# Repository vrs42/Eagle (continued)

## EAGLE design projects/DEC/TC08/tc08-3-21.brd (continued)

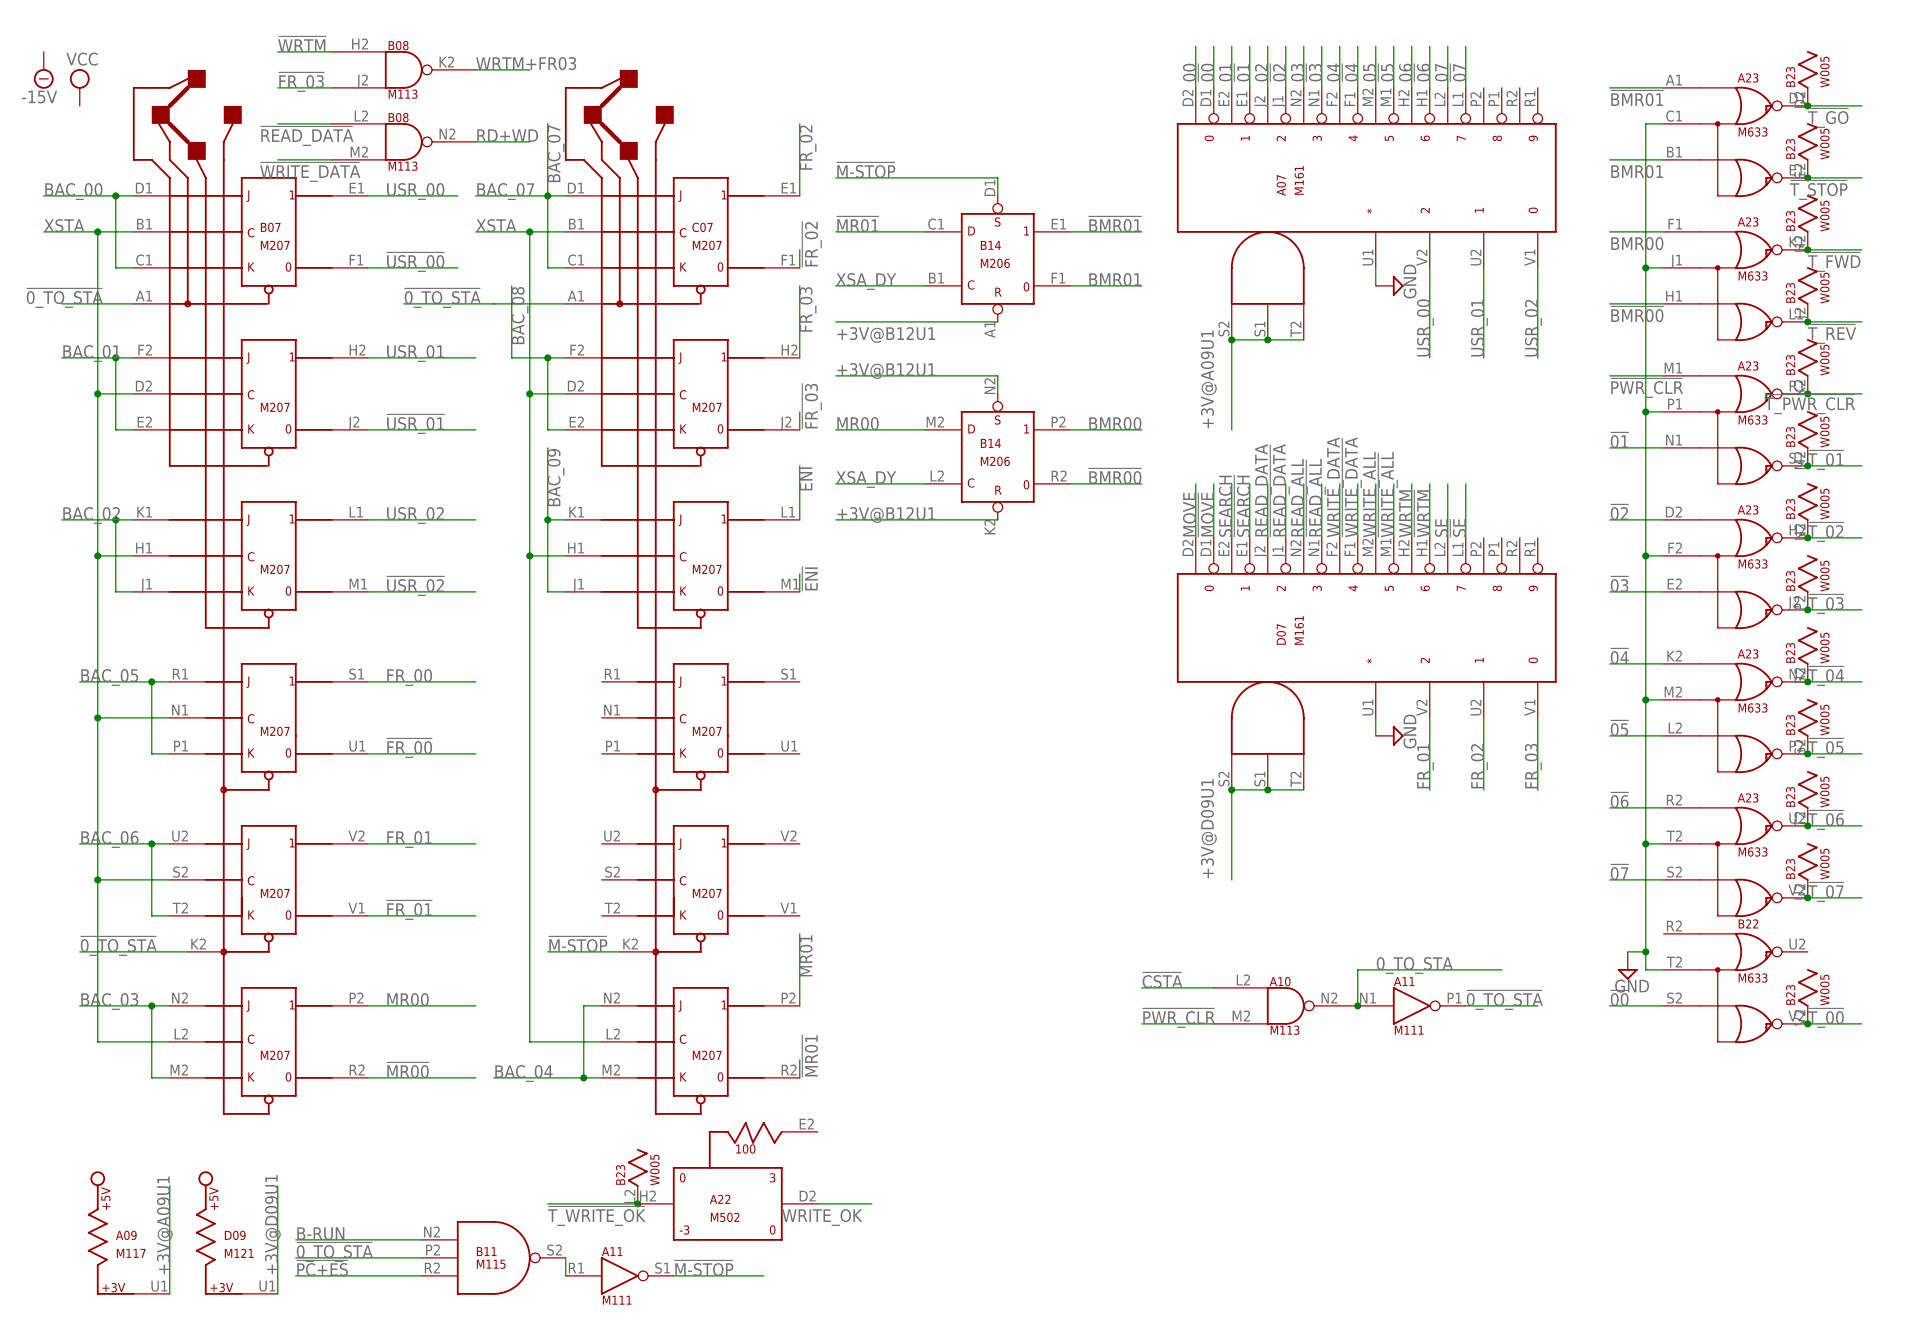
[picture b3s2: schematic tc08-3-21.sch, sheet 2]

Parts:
A07: M161; H807
A09: M117; H807
A10: M113; H807
A11: M111; H807
A22: M502; H807
A23: M633; H807
B07: M207; H807
B08: M113; H807
B11: M115; H807
B14: M206; H807
B22: M633; H807
B23: W005; H807
C07: M207; H807
D07: M161; H807
D09: M121; H807

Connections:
00: A07.D2 (O0)
0_TO_STA: A10.N2 (OUT), A11.N1 (IN)
01: A07.E2 (O1)
02: A07.J2 (O2)
03: A07.N2 (O3)
04: A07.F2 (O4)
05: A07.M2 (O5)
06: A07.H2 (O6)
07: A07.L2 (O7)
!00: A07.D1 (!O0), B22.S2 (B)
!0_TO_STA: A11.P1 (OUT), B07.A1, B07.K2, B11.P2 (IN2), C07.A1
!01: A07.E1 (!O1), A23.N1 (B)
!02: A07.J1 (!O2), A23.D2 (A)
!03: A07.N1 (!O3), A23.E2 (B)
!04: A07.F1 (!O4), A23.K2 (A)
!05: A07.M1 (!O5), A23.L2 (B)
!06: A07.H1 (!O6), A23.R2 (A)
!07: A07.L1 (!O7), A23.S2 (B)
!BMR00: A23.H1 (B), B14.R2 (0)
!BMR01: A23.A1 (A), B14.E1 (1)
!CSTA: A10.L2 (IN1); also elsewhere on the board
!ENI: C07.M1; also elsewhere on the board
!FR_00: B07.U1; also elsewhere on the board
!FR_01: B07.V1; also elsewhere on the board
!FR_02: C07.F1; also elsewhere on the board
!FR_03: B08.J2 (IN2), C07.J2; also elsewhere on the board
!M-STOP: A11.S1 (OUT), B14.D1 (S), C07.K2; also elsewhere on the board
!MOVE: D07.D1 (!O0); also elsewhere on the board
!MR00: B07.R2; also elsewhere on the board
!MR01: B14.C1 (D), C07.R2; also elsewhere on the board
!PC+ES: B11.R2 (IN3); also elsewhere on the board
!PWR_CLR: A10.M2 (IN2), A23.M1 (A); also elsewhere on the board
!READ_ALL: D07.N1 (!O3); also elsewhere on the board
!READ_DATA: B08.L2 (IN1), D07.J1 (!O2); also elsewhere on the board
!SE: D07.L1 (!O7); also elsewhere on the board
!SEARCH: D07.E1 (!O1); also elsewhere on the board
!T_00: B22.V2 (E), B23.V2; also elsewhere on the board
!T_01: A23.S1 (E), B23.M2; also elsewhere on the board
!T_02: A23.H2 (D), B23.N2; also elsewhere on the board
!T_03: A23.J2 (E), B23.P2; also elsewhere on the board
!T_04: A23.N2 (D), B23.R2; also elsewhere on the board
!T_05: A23.P2 (E), B23.S2; also elsewhere on the board
!T_06: A23.U2 (D), B23.T2; also elsewhere on the board
!T_07: A23.V2 (E), B23.U2; also elsewhere on the board
!T_FWD: A23.K1 (D), B23.H2; also elsewhere on the board
!T_GO: A23.D1 (D), B23.D2; also elsewhere on the board
!T_PWR_CLR: A23.R1 (D), B23.K2; also elsewhere on the board
!T_REV: A23.L1 (E), B23.J2; also elsewhere on the board
!T_STOP: A23.E1 (E), B23.E2; also elsewhere on the board
!T_WRITE_OK: A22.H2, B23.L2; also elsewhere on the board
!USR_00: B07.F1; also elsewhere on the board
!USR_01: B07.J2; also elsewhere on the board
!USR_02: B07.M1; also elsewhere on the board
!WRITE_ALL: D07.M1 (!O5)
!WRITE_DATA: B08.M2 (IN2), D07.F1 (!O4)
!WRTM: B08.H2 (IN1), D07.H1 (!O6); also elsewhere on the board
+3V@A09U1: A07.S1 (EN2), A07.S2 (EN1), A07.T2 (EN3), A09.U1; also elsewhere on the board
+3V@B12U1: B14.A1 (R), B14.K2 (R), B14.N2 (S); also elsewhere on the board
+3V@D09U1: D07.S1 (EN2), D07.S2 (EN1), D07.T2 (EN3), D09.U1
-15V: A22.B2 (-15V), A23.B2 (-15V), B22.B2 (-15V), B23.B2 (-15V); also elsewhere on the board
B-RUN: B11.N2 (IN1); also elsewhere on the board
BAC_00: B07.C1, B07.D1; also elsewhere on the board
BAC_01: B07.E2, B07.F2; also elsewhere on the board
BAC_02: B07.J1, B07.K1; also elsewhere on the board
BAC_03: B07.M2, B07.N2; also elsewhere on the board
BAC_04: C07.M2, C07.N2; also elsewhere on the board
BAC_05: B07.P1, B07.R1; also elsewhere on the board
BAC_06: B07.T2, B07.U2; also elsewhere on the board
BAC_07: C07.C1, C07.D1; also elsewhere on the board
BAC_08: C07.E2, C07.F2; also elsewhere on the board
BAC_09: C07.J1, C07.K1; also elsewhere on the board
BMR00: A23.F1 (A), B14.P2 (1)
BMR01: A23.B1 (B), B14.F1 (0)
ENI: C07.L1; also elsewhere on the board
FR_00: B07.S1; also elsewhere on the board
FR_01: B07.V2, D07.V2 (IN2); also elsewhere on the board
FR_02: C07.E1, D07.U2 (IN1); also elsewhere on the board
FR_03: C07.H2, D07.V1 (IN0); also elsewhere on the board
GND: A07.C2 (GND), A07.T1 (GND), A07.U1 (IN*), A09.C2 (GND), A09.T1 (GND), A10.C2 (GND), A10.T1 (GND), A11.C2 (GND), A11.T1 (GND), A22.C2 (GND), A22.M2 (GND), A23.C1 (C), A23.C2 (GND), A23.F2 (C), A23.J1 (C), A23.M2 (C), A23.P1 (C), A23.T1 (GND), A23.T2 (C), A23.U1 (GND), A23.V1 (GND), B07.C2 (GND), B07.T1 (GND), B08.C2 (GND), B08.T1 (GND), B11.C2 (GND), B11.T1 (GND), B14.C2 (GND), B14.T1 (GND), B22.C2 (GND), B22.T1 (GND), B22.T2 (C), B22.U1 (GND), B22.V1 (GND), B23.C2 (GND), C07.C2 (GND), C07.T1 (GND), D07.C2 (GND), D07.T1 (GND), D07.U1 (IN*), D09.C2 (GND), D09.T1 (GND); also elsewhere on the board
MOVE: D07.D2 (O0)
MR00: B07.P2, B14.M2 (D); also elsewhere on the board
MR01: C07.P2; also elsewhere on the board
unnamed: A11.R1 (IN), B11.S2 (OUT)
RD+WD: B08.N2 (OUT); also elsewhere on the board
READ_ALL: D07.N2 (O3)
READ_DATA: D07.J2 (O2); also elsewhere on the board
SE: D07.L2 (O7)
SEARCH: D07.E2 (O1); also elsewhere on the board
USR_00: A07.V2 (IN2), B07.E1; also elsewhere on the board
USR_01: A07.U2 (IN1), B07.H2; also elsewhere on the board
USR_02: A07.V1 (IN0), B07.L1; also elsewhere on the board
VCC: A07.A2 (VCC), A09.A2 (VCC), A10.A2 (VCC), A11.A2 (VCC), A22.A2 (VCC), A23.A2 (VCC), B07.A2 (VCC), B08.A2 (VCC), B11.A2 (VCC), B14.A2 (VCC), B22.A2 (VCC), B23.A2 (VCC), C07.A2 (VCC), D07.A2 (VCC), D09.A2 (VCC); also elsewhere on the board
WRITE_ALL: D07.M2 (O5); also elsewhere on the board
WRITE_DATA: D07.F2 (O4); also elsewhere on the board
WRITE_OK: A22.D2; also elsewhere on the board
WRTM: D07.H2 (O6); also elsewhere on the board
WRTM+FR03: B08.K2 (OUT); also elsewhere on the board
XSA_DY: B14.B1 (C), B14.L2 (C); also elsewhere on the board
XSTA: B07.B1, B07.D2, B07.H1, B07.L2, B07.N1, B07.S2, C07.B1, C07.D2, C07.H1, C07.L2; also elsewhere on the board

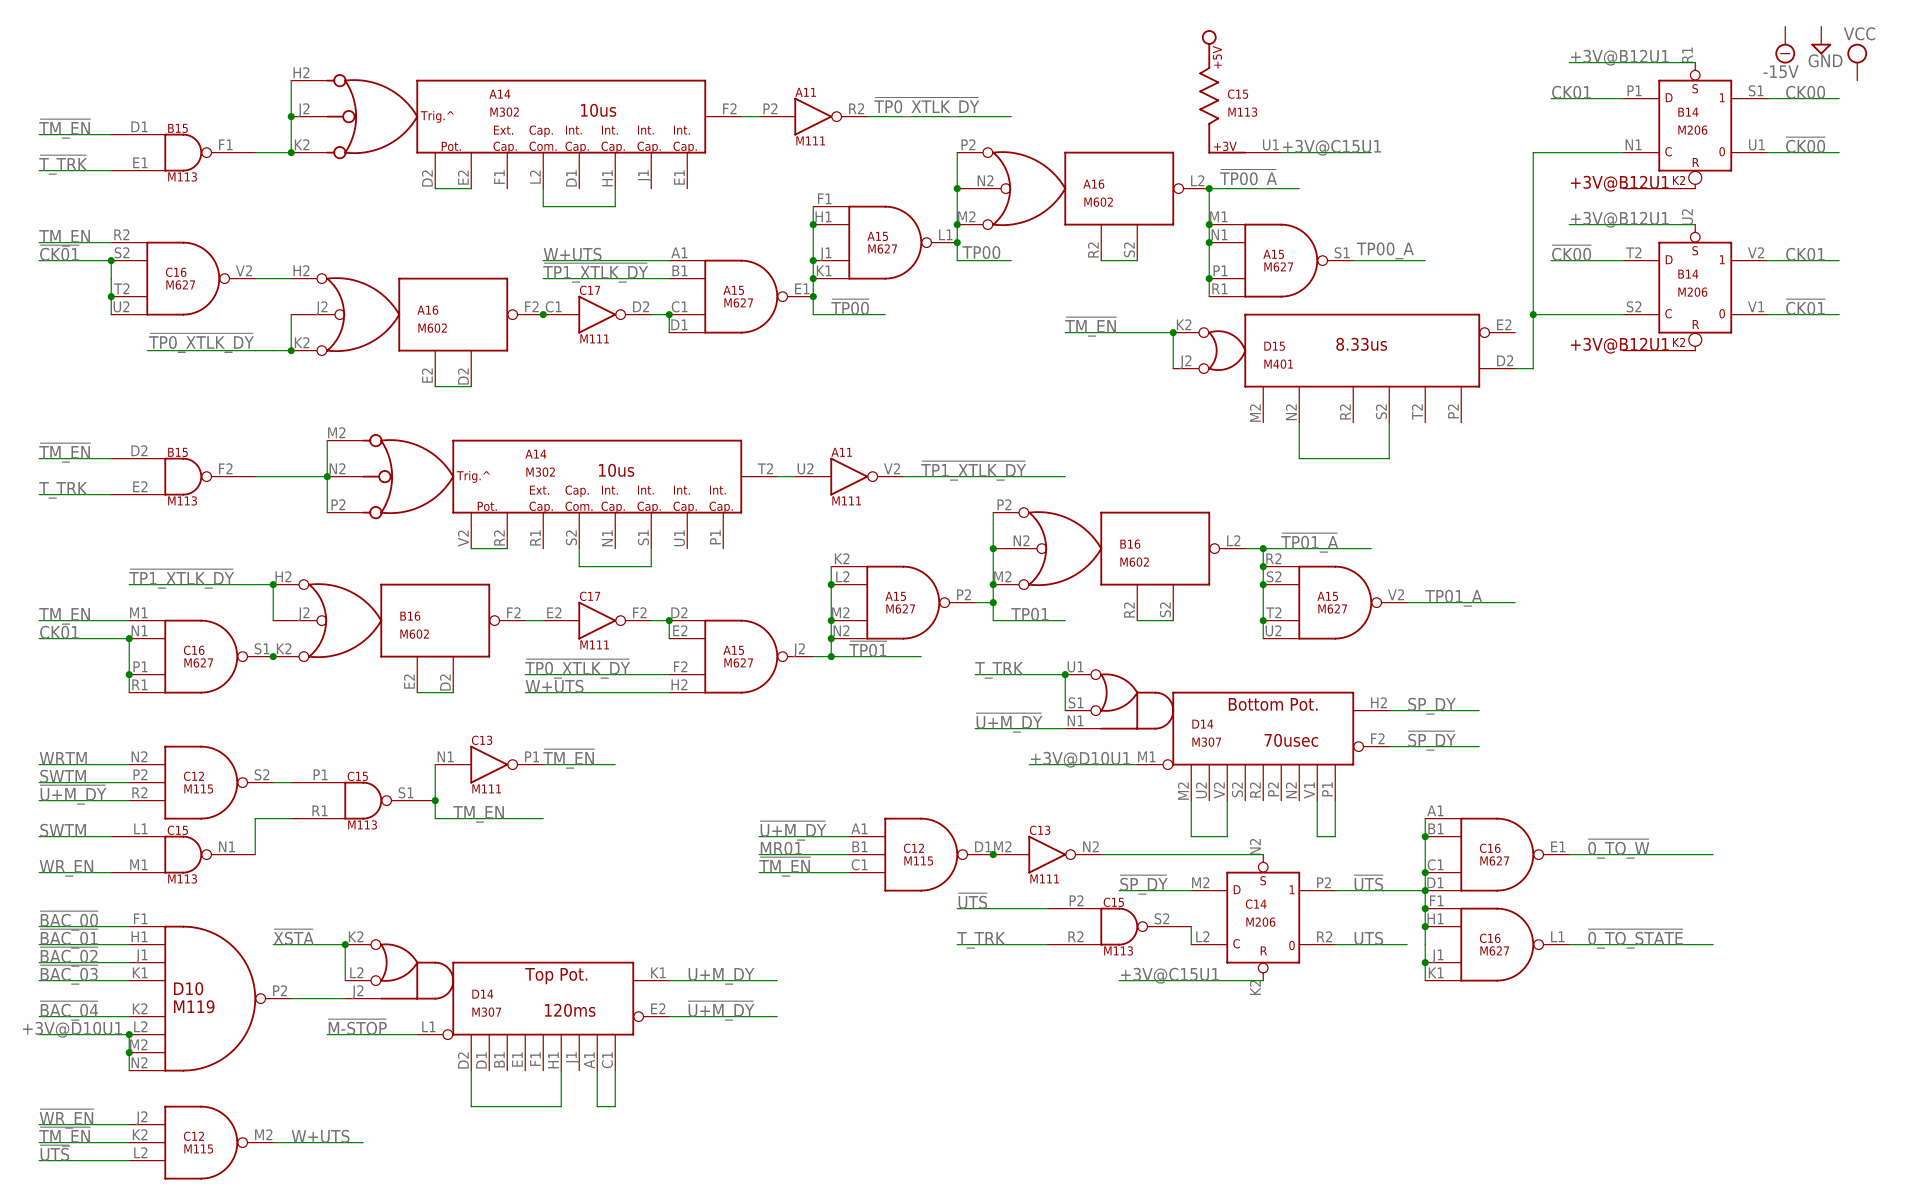
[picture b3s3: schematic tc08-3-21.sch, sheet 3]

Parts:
A11: M111; H807
A14: M302; H807
A15: M627; H807
A16: M602; H807
B14: M206; H807
B15: M113; H807
B16: M602; H807
C12: M115; H807
C13, C17: M111; H807
C14: M206; H807
C15: M113; H807
C16: M627; H807
D10: M119; H807
D14: M307; H807
D15: M401; H807

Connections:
!0_TO_STATE: C16.L1 (OUT); also elsewhere on the board
!0_TO_W: C16.E1 (OUT); also elsewhere on the board
!BAC_00: D10.F1 (IN1); also elsewhere on the board
!BAC_01: D10.H1 (IN2); also elsewhere on the board
!BAC_02: D10.J1 (IN3); also elsewhere on the board
!BAC_03: D10.K1 (IN4); also elsewhere on the board
!BAC_04: D10.K2 (IN5); also elsewhere on the board
!CK00: B14.T2 (D), B14.U1 (0); also elsewhere on the board
!CK01: B14.V1 (0), C16.S2 (IN2), C16.T2 (IN3), C16.U2 (IN4)
!M-STOP: D14.L1 (M1); also elsewhere on the board
!SP_DY: C14.M2 (D), D14.F2
!TM_EN: B15.D1 (IN1), B15.D2 (IN1), C12.C1 (IN3), C12.K2 (IN2), C13.P1 (OUT), D15.J2, D15.K2
!TP00: A15.E1 (OUT), A15.F1 (IN1), A15.H1 (IN2), A15.J1 (IN3), A15.K1 (IN4); also elsewhere on the board
!TP00_A: A15.M1 (IN1), A15.N1 (IN2), A15.P1 (IN3), A15.R1 (IN4), A16.L2 (F2)
!TP0_XTLK_DY: A11.R2 (OUT), A15.F2 (IN3), A16.J2, A16.K2
!TP01: A15.J2 (OUT), A15.K2 (IN1), A15.L2 (IN2), A15.M2 (IN3), A15.N2 (IN4); also elsewhere on the board
!TP01_A: A15.R2 (IN1), A15.S2 (IN2), A15.T2 (IN3), A15.U2 (IN4), B16.L2 (F2)
!TP1_XTLK_DY: A11.V2 (OUT), A15.B1 (IN2), B16.H2, B16.J2
!T_TRK: B15.E1 (IN2); also elsewhere on the board
!U+M_DY: C12.A1 (IN1), C12.R2 (IN3), D14.E2 (F2), D14.N1
!UTS: C12.L2 (IN3), C14.P2 (1), C15.P2 (IN1), C16.A1 (IN1), C16.B1 (IN2), C16.C1 (IN3), C16.D1 (IN4), C16.F1 (IN1), C16.H1 (IN2), C16.J1 (IN3), C16.K1 (IN4)
!WR_EN: C12.J2 (IN1); also elsewhere on the board
!XSTA: D14.K2 (U1), D14.L2 (S1); also elsewhere on the board
+3V@B12U1: B14.R1 (S), B14.U2 (S); also elsewhere on the board
+3V@C15U1: C14.K2 (R), C15.U1; also elsewhere on the board
+3V@D10U1: D10.L2 (IN6), D10.M2 (IN7), D10.N2 (IN8), D14.M1; also elsewhere on the board
-15V: D14.B2 (-15V); also elsewhere on the board
CK00: B14.S1 (1); also elsewhere on the board
CK01: B14.P1 (D), B14.V2 (1), C16.N1 (IN2), C16.P1 (IN3), C16.R1 (IN4)
GND: A11.C2 (GND), A11.T1 (GND), A14.C2 (GND), A14.T1 (GND), A15.C2 (GND), A15.T1 (GND), A16.C2 (GND), B14.C2 (GND), B14.T1 (GND), B15.C2 (GND), B15.T1 (GND), B16.C2 (GND), C12.C2 (GND), C12.T1 (GND), C13.C2 (GND), C13.T1 (GND), C14.C2 (GND), C14.T1 (GND), C15.C2 (GND), C15.T1 (GND), C16.C2 (GND), C16.T1 (GND), C17.C2 (GND), C17.T1 (GND), D10.C2 (GND), D10.T1 (GND), D14.C2 (GND), D14.T1 (GND), D15.C2 (GND); also elsewhere on the board
MR01: C12.B1 (IN2); also elsewhere on the board
unnamed: A16.H2, C16.V2 (OUT)
unnamed: A14.H2, A14.J2, A14.K2, B15.F1 (OUT)
unnamed: A16.D2, A16.E2
unnamed: A16.F2, C17.C1 (IN)
unnamed: A15.C1 (IN3), A15.D1 (IN4), C17.D2 (OUT)
unnamed: B14.N1 (C), B14.S2 (C), D15.D2
unnamed: A14.M2 (H2), A14.N2 (J2), A14.P2 (K2), B15.F2 (OUT)
unnamed: A14.H1, A14.L2
unnamed: A16.R2 (E2), A16.S2 (D2)
unnamed: A14.D2, A14.E2
unnamed: A11.U2 (IN), A14.T2 (F2)
unnamed: A11.P2 (IN), A14.F2
unnamed: B16.K2, C16.S1 (OUT)
unnamed: A14.R2 (E2), A14.V2 (D2)
unnamed: A14.S1 (H1), A14.S2 (L2)
unnamed: D15.N2, D15.S2
unnamed: B16.D2, B16.E2
unnamed: B16.F2, C17.E2 (IN)
unnamed: A15.D2 (IN1), A15.E2 (IN2), C17.F2 (OUT)
unnamed: B16.R2 (E2), B16.S2 (D2)
unnamed: D14.M2, D14.V2
unnamed: D14.P1, D14.V1
unnamed: C12.S2 (OUT), C15.P1 (IN1)
unnamed: C15.N1 (OUT), C15.R1 (IN2)
unnamed: D10.P2 (OUT), D14.J2 (N1)
unnamed: D14.D2 (M2), D14.H1 (P2)
unnamed: D14.A1 (V1), D14.C1 (P1)
unnamed: C14.L2 (C), C15.S2 (OUT)
unnamed: C13.N2 (OUT), C14.N2 (S)
unnamed: C12.D1 (OUT), C13.M2 (IN)
SP_DY: D14.H2
SWTM: C12.P2 (IN2), C15.L1 (IN1); also elsewhere on the board
TM_EN: C13.N1 (IN), C15.S1 (OUT), C16.M1 (IN1), C16.R2 (IN1); also elsewhere on the board
TP00: A15.L1 (OUT), A16.M2 (K2), A16.N2 (J2), A16.P2 (H2); also elsewhere on the board
TP00_A: A15.S1 (OUT); also elsewhere on the board
TP01: A15.P2 (OUT), B16.M2 (K2), B16.N2 (J2), B16.P2 (H2); also elsewhere on the board
TP01_A: A15.V2 (OUT); also elsewhere on the board
T_TRK: B15.E2 (IN2), C15.R2 (IN2), D14.S1, D14.U1; also elsewhere on the board
U+M_DY: D14.K1 (H2)
UTS: C14.R2 (0); also elsewhere on the board
VCC: A11.A2 (VCC), A14.A2 (VCC), A15.A2 (VCC), A16.A2 (VCC), B14.A2 (VCC), B15.A2 (VCC), B16.A2 (VCC), C12.A2 (VCC), C13.A2 (VCC), C14.A2 (VCC), C15.A2 (VCC), C16.A2 (VCC), C17.A2 (VCC), D10.A2 (VCC), D14.A2 (VCC), D15.A2 (VCC); also elsewhere on the board
W+UTS: A15.A1 (IN1), A15.H2 (IN4), C12.M2 (OUT)
WRTM: C12.N2 (IN1); also elsewhere on the board
WR_EN: C15.M1 (IN2); also elsewhere on the board

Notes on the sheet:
+3V@B12U1
8.33us
120ms
Top Pot.
Bottom Pot.
70usec
10us

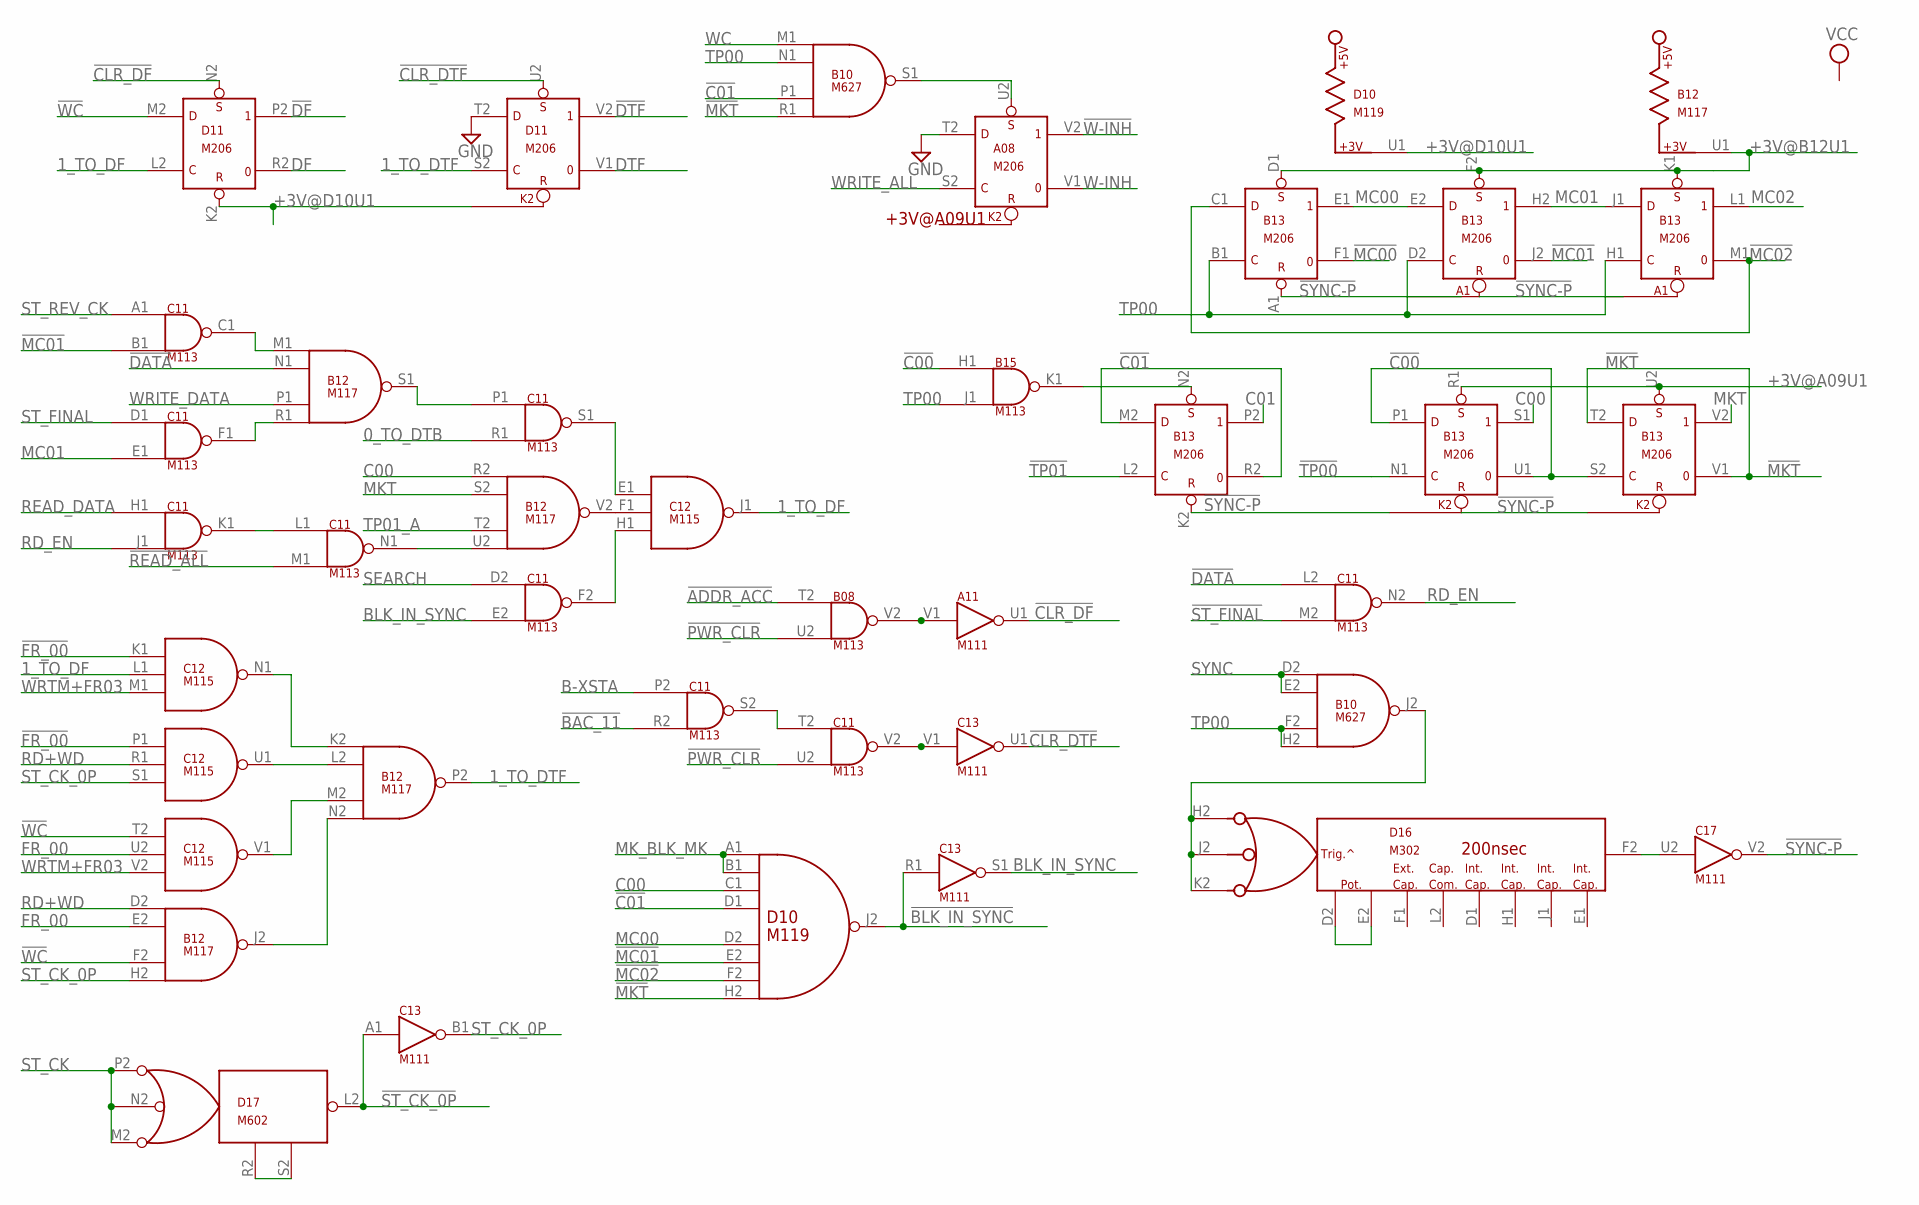
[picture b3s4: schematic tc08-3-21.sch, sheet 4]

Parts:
A08: M206; H807
A11: M111; H807
B08, B15: M113; H807
B10: M627; H807
B12: M117; H807
B13: M206; H807
C11: M113; H807
C12: M115; H807
C13, C17: M111; H807
D10: M119; H807
D11: M206; H807
D16: M302; H807
D17: M602; H807

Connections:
0_TO_DTB: C11.R1 (IN2); also elsewhere on the board
1_TO_DF: C12.J1 (OUT), C12.L1 (IN2), D11.L2 (C); also elsewhere on the board
1_TO_DTF: B12.P2 (OUT), D11.S2 (C)
!ADDR_ACC: B08.T2 (IN1); also elsewhere on the board
!BAC_11: C11.R2 (IN2); also elsewhere on the board
!BLK_IN_SYNC: C13.R1 (IN), D10.J2 (OUT); also elsewhere on the board
!C00: B13.P1 (D), B13.S2 (C), B13.U1 (0), B15.H1 (IN1); also elsewhere on the board
!C01: B10.P1 (IN3), B13.M2 (D), B13.R2 (0), D10.D1 (IN4); also elsewhere on the board
!CLR_DF: A11.U1 (OUT), D11.N2 (S)
!CLR_DTF: C13.U1 (OUT), D11.U2 (S)
!DATA: B12.N1 (IN2), C11.L2 (IN1); also elsewhere on the board
!DF: D11.P2 (1); also elsewhere on the board
!DTF: D11.V2 (1); also elsewhere on the board
!FR_00: C12.K1 (IN1), C12.P1 (IN1); also elsewhere on the board
!MC00: B13.F1 (0); also elsewhere on the board
!MC01: B13.J2 (0), C11.B1 (IN2), D10.E2 (IN6); also elsewhere on the board
!MC02: B13.C1 (D), B13.M1 (0), D10.F2 (IN7)
!MKT: B10.R1 (IN4), B13.T2 (D), B13.V1 (0), D10.H2 (IN8); also elsewhere on the board
!PWR_CLR: B08.U2 (IN2), C11.U2 (IN2); also elsewhere on the board
!READ_ALL: C11.M1 (IN2); also elsewhere on the board
!ST_CK_0P: C13.A1 (IN), D17.L2 (F2)
!ST_FINAL: C11.M2 (IN2); also elsewhere on the board
!SYNC-P: B13.A1 (R), B13.K2 (R), C17.V2 (OUT)
!TP00: B13.N1 (C); also elsewhere on the board
!TP01: B13.L2 (C); also elsewhere on the board
!W-INH: A08.V2 (1); also elsewhere on the board
!WC: B12.F2 (IN3), C12.T2 (IN1), D11.M2 (D); also elsewhere on the board
+3V@A09U1: B13.R1 (S), B13.U2 (S); also elsewhere on the board
+3V@B12U1: B12.U1, B13.D1 (S), B13.F2 (S), B13.K1 (S); also elsewhere on the board
+3V@D10U1: D10.U1, D11.K2 (R); also elsewhere on the board
B10J2: B10.J2 (OUT), D16.H2, D16.J2, D16.K2
B-XSTA: C11.P2 (IN1); also elsewhere on the board
BLK_IN_SYNC: C11.E2 (IN2), C13.S1 (OUT); also elsewhere on the board
C00: B12.R2 (IN1), B13.S1 (1), D10.C1 (IN3); also elsewhere on the board
C01: B13.P2 (1); also elsewhere on the board
D16F2: C17.U2 (IN), D16.F2
DF: D11.R2 (0); also elsewhere on the board
DTF: D11.V1 (0); also elsewhere on the board
FR_00: B12.E2 (IN2), C12.U2 (IN2); also elsewhere on the board
GND: A08.C2 (GND), A08.T1 (GND), A08.T2 (D), A11.C2 (GND), A11.T1 (GND), B08.C2 (GND), B08.T1 (GND), B10.C2 (GND), B10.T1 (GND), B12.C2 (GND), B12.T1 (GND), B13.C2 (GND), B13.T1 (GND), B15.C2 (GND), B15.T1 (GND), C11.C2 (GND), C11.T1 (GND), C12.C2 (GND), C12.T1 (GND), C13.C2 (GND), C13.T1 (GND), C17.C2 (GND), C17.T1 (GND), D10.C2 (GND), D10.T1 (GND), D11.C2 (GND), D11.T1 (GND), D11.T2 (D), D16.C2 (GND), D16.T1 (GND), D17.C2 (GND); also elsewhere on the board
MC00: B13.E1 (1), B13.E2 (D), D10.D2 (IN5); also elsewhere on the board
MC01: B13.H2 (1), B13.J1 (D), C11.E1 (IN2); also elsewhere on the board
MC02: B13.L1 (1); also elsewhere on the board
MKT: B12.S2 (IN2), B13.V2 (1); also elsewhere on the board
MK_BLK_MK: D10.A1 (IN1), D10.B1 (IN2); also elsewhere on the board
unnamed: B12.M1 (IN1), C11.C1 (OUT)
unnamed: B12.R1 (IN4), C11.F1 (OUT)
unnamed: B12.L2 (IN2), C12.U1 (OUT)
unnamed: A08.U2 (S), B10.S1 (OUT)
unnamed: C11.K1 (OUT), C11.L1 (IN1)
unnamed: B12.U2 (IN4), C11.N1 (OUT)
unnamed: B12.S1 (OUT), C11.P1 (IN1)
unnamed: B12.V2 (OUT), C12.F1 (IN2)
unnamed: C11.S1 (OUT), C12.E1 (IN1)
unnamed: C11.F2 (OUT), C12.H1 (IN3)
unnamed: D16.D2, D16.E2
unnamed: A11.V1 (IN), B08.V2 (OUT)
unnamed: C11.V2 (OUT), C13.V1 (IN)
unnamed: B12.K2 (IN1), C12.N1 (OUT)
unnamed: B12.M2 (IN3), C12.V1 (OUT)
unnamed: B12.J2 (OUT), B12.N2 (IN4)
unnamed: B13.N2 (S), B15.K1 (OUT)
unnamed: C11.S2 (OUT), C11.T2 (IN1)
unnamed: D17.R2 (E2), D17.S2 (D2)
RD+WD: B12.D2 (IN1), C12.R1 (IN2); also elsewhere on the board
RD_EN: C11.J1 (IN2), C11.N2 (OUT)
READ_DATA: C11.H1 (IN1); also elsewhere on the board
SEARCH: C11.D2 (IN1); also elsewhere on the board
ST_CK: D17.M2 (K2), D17.N2 (J2), D17.P2 (H2); also elsewhere on the board
ST_CK_0P: B12.H2 (IN4), C12.S1 (IN3), C13.B1 (OUT)
ST_FINAL: C11.D1 (IN1); also elsewhere on the board
ST_REV_CK: C11.A1 (IN1); also elsewhere on the board
SYNC: B10.D2 (IN1), B10.E2 (IN2); also elsewhere on the board
TP00: B10.F2 (IN3), B10.H2 (IN4), B10.N1 (IN2), B13.B1 (C), B13.D2 (C), B13.H1 (C), B15.J1 (IN2); also elsewhere on the board
TP01_A: B12.T2 (IN3); also elsewhere on the board
VCC: A08.A2 (VCC), A11.A2 (VCC), B08.A2 (VCC), B10.A2 (VCC), B12.A2 (VCC), B13.A2 (VCC), B15.A2 (VCC), C11.A2 (VCC), C12.A2 (VCC), C13.A2 (VCC), C17.A2 (VCC), D10.A2 (VCC), D11.A2 (VCC), D16.A2 (VCC), D17.A2 (VCC); also elsewhere on the board
W-INH: A08.V1 (0)
WC: B10.M1 (IN1); also elsewhere on the board
WRITE_ALL: A08.S2 (C); also elsewhere on the board
WRITE_DATA: B12.P1 (IN3); also elsewhere on the board
WRTM+FR03: C12.M1 (IN3), C12.V2 (IN3); also elsewhere on the board

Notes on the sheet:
+3V@A09U1
200nsec

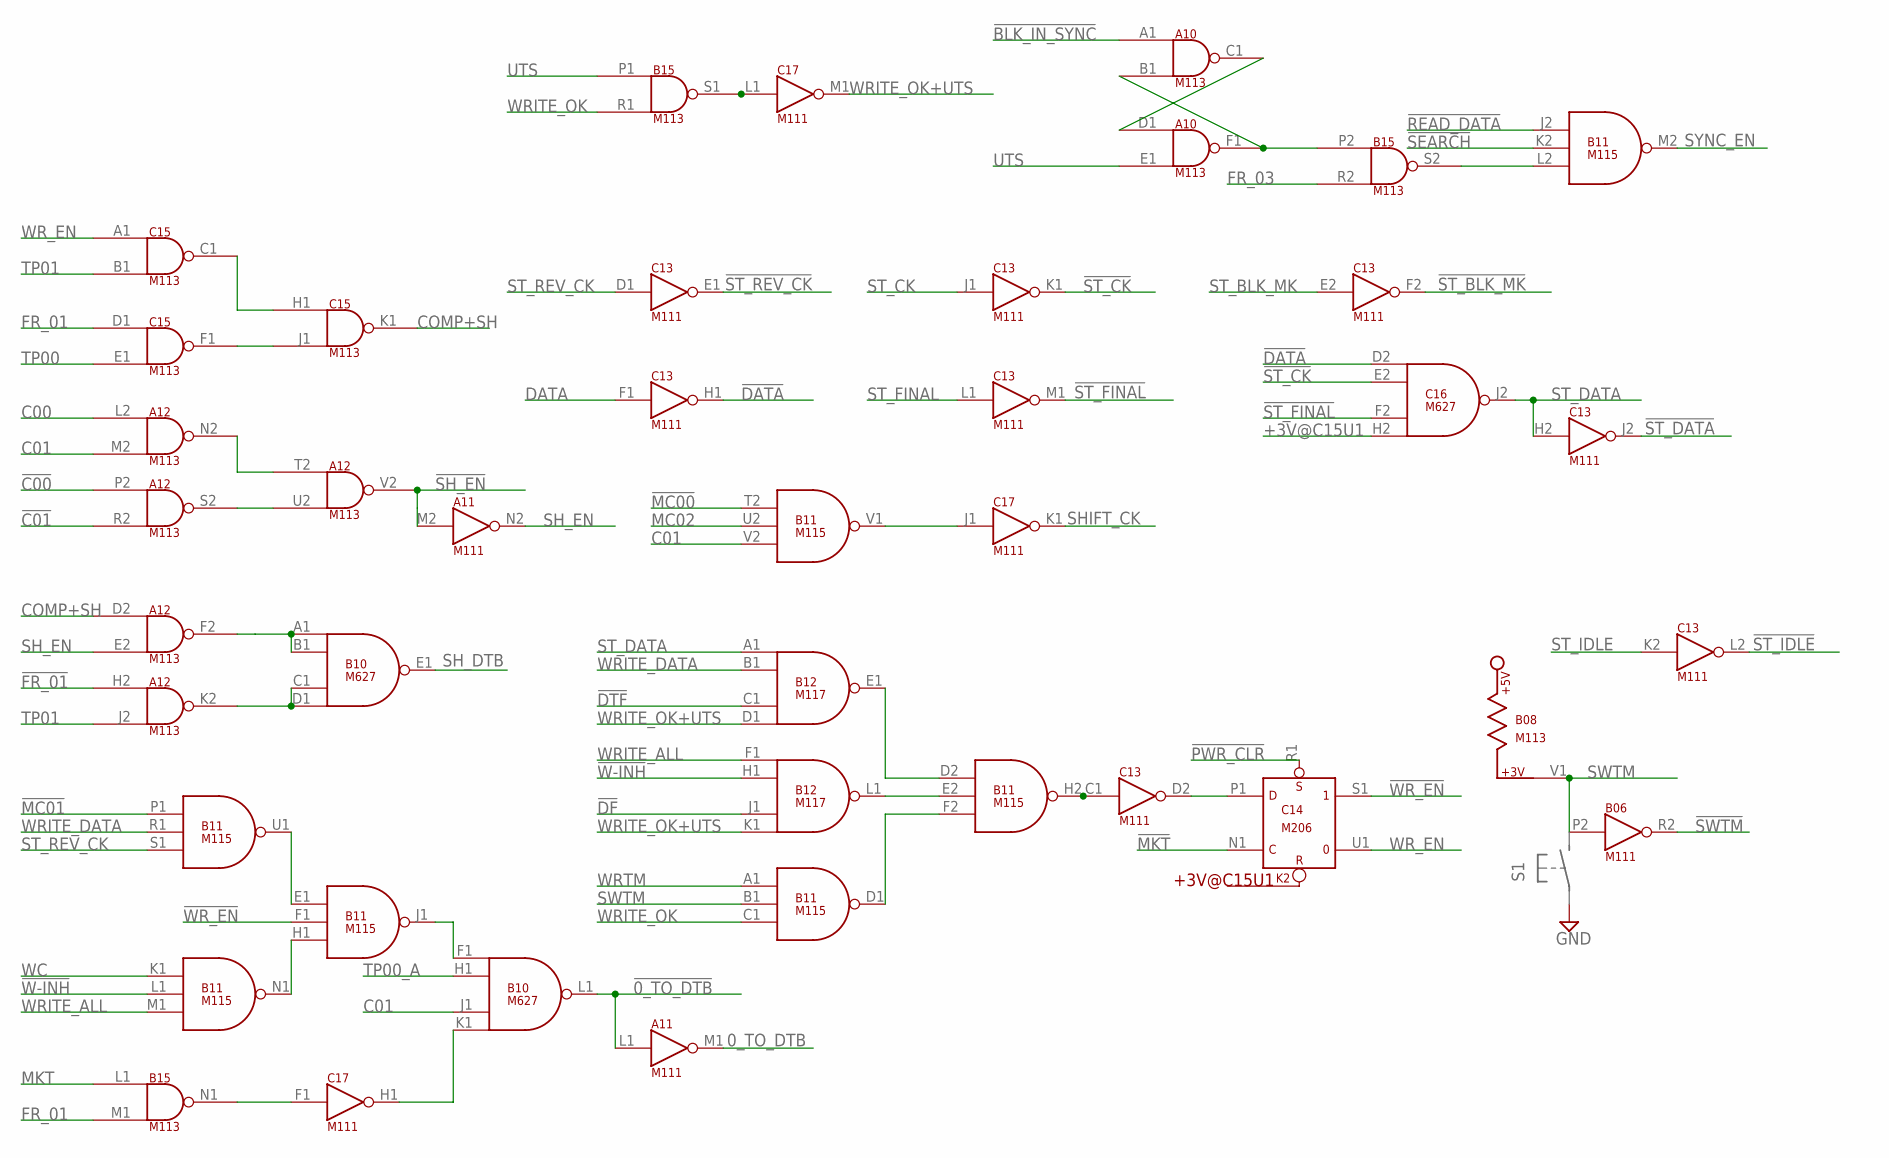
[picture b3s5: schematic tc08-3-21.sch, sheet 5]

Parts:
A10, A12: M113; H807
A11: M111; H807
B06: M111; H807
B08, B15: M113; H807
B10: M627; H807
B11: M115; H807
B12: M117; H807
C13, C17: M111; H807
C14: M206; H807
C15: M113; H807
C16: M627; H807

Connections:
0_TO_DTB: A11.M1 (OUT); also elsewhere on the board
!0_TO_DTB: A11.L1 (IN), B10.L1 (OUT); also elsewhere on the board
!BLK_IN_SYNC: A10.A1 (IN1); also elsewhere on the board
!C00: A12.P2 (IN1); also elsewhere on the board
!C01: A12.R2 (IN2); also elsewhere on the board
!DATA: C13.H1 (OUT), C16.D2 (IN1); also elsewhere on the board
!DF: B12.J1 (IN3); also elsewhere on the board
!DTF: B12.C1 (IN3); also elsewhere on the board
!FR_01: A12.H2 (IN1); also elsewhere on the board
!MC00: B11.T2 (IN1); also elsewhere on the board
!MC01: B11.P1 (IN1); also elsewhere on the board
!MKT: C14.N1 (C); also elsewhere on the board
!PWR_CLR: C14.R1 (S); also elsewhere on the board
!READ_DATA: B11.J2 (IN1); also elsewhere on the board
!SEARCH: B11.K2 (IN2); also elsewhere on the board
!SH_EN: A11.M2 (IN), A12.V2 (OUT); also elsewhere on the board
!ST_BLK_MK: C13.F2 (OUT); also elsewhere on the board
!ST_CK: C13.K1 (OUT), C16.E2 (IN2)
!ST_DATA: C13.J2 (OUT)
!ST_FINAL: C13.M1 (OUT), C16.F2 (IN3); also elsewhere on the board
!ST_IDLE: C13.L2 (OUT); also elsewhere on the board
!ST_REV_CK: C13.E1 (OUT)
!SWTM: B06.R2 (OUT); also elsewhere on the board
!W-INH: B11.L1 (IN2), B12.H1 (IN2); also elsewhere on the board
!WR_EN: B11.F1 (IN2), C14.S1 (1); also elsewhere on the board
+3V@C15U1: C16.H2 (IN4); also elsewhere on the board
C00: A12.L2 (IN1); also elsewhere on the board
C01: A12.M2 (IN2), B10.J1 (IN3), B11.V2 (IN3); also elsewhere on the board
COMP+SH: A12.D2 (IN1), C15.K1 (OUT); also elsewhere on the board
DATA: C13.F1 (IN); also elsewhere on the board
FR_01: B15.M1 (IN2), C15.D1 (IN1); also elsewhere on the board
FR_03: B15.R2 (IN2); also elsewhere on the board
GND: A10.C2 (GND), A10.T1 (GND), A11.C2 (GND), A11.T1 (GND), A12.C2 (GND), A12.T1 (GND), B06.C2 (GND), B06.T1 (GND), B08.C2 (GND), B08.T1 (GND), B10.C2 (GND), B10.T1 (GND), B11.C2 (GND), B11.T1 (GND), B12.C2 (GND), B12.T1 (GND), B15.C2 (GND), B15.T1 (GND), C13.C2 (GND), C13.T1 (GND), C14.C2 (GND), C14.T1 (GND), C15.C2 (GND), C15.T1 (GND), C16.C2 (GND), C16.T1 (GND), C17.C2 (GND), C17.T1 (GND); also elsewhere on the board
MC02: B11.U2 (IN2); also elsewhere on the board
MKT: B15.L1 (IN1); also elsewhere on the board
unnamed: B15.S1 (OUT), C17.L1 (IN)
unnamed: C13.D2 (OUT), C14.P1 (D)
unnamed: C15.C1 (OUT), C15.H1 (IN1)
unnamed: C15.F1 (OUT), C15.J1 (IN2)
unnamed: A12.N2 (OUT), A12.T2 (IN1)
unnamed: A12.S2 (OUT), A12.U2 (IN2)
unnamed: B11.H2 (OUT), C13.C1 (IN)
unnamed: B11.E2 (IN2), B12.L1 (OUT)
unnamed: B11.D2 (IN1), B12.E1 (OUT)
unnamed: B11.D1 (OUT), B11.F2 (IN3)
unnamed: A12.K2 (OUT), B10.C1 (IN3), B10.D1 (IN4)
unnamed: A12.F2 (OUT), B10.A1 (IN1), B10.B1 (IN2)
unnamed: B11.E1 (IN1), B11.U1 (OUT)
unnamed: B15.N1 (OUT), C17.F1 (IN)
unnamed: B11.H1 (IN3), B11.N1 (OUT)
unnamed: B10.F1 (IN1), B11.J1 (OUT)
unnamed: B10.K1 (IN4), C17.H1 (OUT)
unnamed: B11.V1 (OUT), C17.J1 (IN)
unnamed: A10.C1 (OUT), A10.D1 (IN1)
unnamed: A10.B1 (IN2), A10.F1 (OUT), B15.P2 (IN1)
unnamed: B11.L2 (IN3), B15.S2 (OUT)
SHIFT_CK: C17.K1 (OUT); also elsewhere on the board
SH_DTB: B10.E1 (OUT); also elsewhere on the board
SH_EN: A11.N2 (OUT), A12.E2 (IN2); also elsewhere on the board
ST_BLK_MK: C13.E2 (IN); also elsewhere on the board
ST_CK: C13.J1 (IN); also elsewhere on the board
ST_DATA: B12.A1 (IN1), C13.H2 (IN), C16.J2 (OUT)
ST_FINAL: C13.L1 (IN); also elsewhere on the board
ST_IDLE: C13.K2 (IN); also elsewhere on the board
ST_REV_CK: B11.S1 (IN3), C13.D1 (IN); also elsewhere on the board
SWTM: B06.P2 (IN), B08.V1, B11.B1 (IN2); also elsewhere on the board
SYNC_EN: B11.M2 (OUT); also elsewhere on the board
TP00: C15.E1 (IN2); also elsewhere on the board
TP00_A: B10.H1 (IN2); also elsewhere on the board
TP01: A12.J2 (IN2), C15.B1 (IN2); also elsewhere on the board
UTS: A10.E1 (IN2), B15.P1 (IN1); also elsewhere on the board
VCC: A10.A2 (VCC), A11.A2 (VCC), A12.A2 (VCC), B06.A2 (VCC), B08.A2 (VCC), B10.A2 (VCC), B11.A2 (VCC), B12.A2 (VCC), B15.A2 (VCC), C13.A2 (VCC), C14.A2 (VCC), C15.A2 (VCC), C16.A2 (VCC), C17.A2 (VCC); also elsewhere on the board
WC: B11.K1 (IN1); also elsewhere on the board
WRITE_ALL: B11.M1 (IN3), B12.F1 (IN1); also elsewhere on the board
WRITE_DATA: B11.R1 (IN2), B12.B1 (IN2); also elsewhere on the board
WRITE_OK: B11.C1 (IN3), B15.R1 (IN2); also elsewhere on the board
WRITE_OK+UTS: B12.D1 (IN4), B12.K1 (IN4), C17.M1 (OUT)
WRTM: B11.A1 (IN1); also elsewhere on the board
WR_EN: C14.U1 (0), C15.A1 (IN1); also elsewhere on the board

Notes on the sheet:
+3V@C15U1
